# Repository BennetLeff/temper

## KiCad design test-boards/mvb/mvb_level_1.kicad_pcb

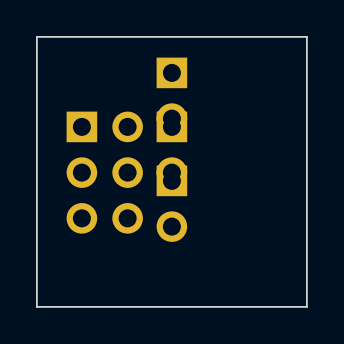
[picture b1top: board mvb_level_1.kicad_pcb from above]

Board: 2 copper layers, 15.0 x 15.0 mm, 4 parts (0 on the bottom side), 6 nets, no tracks yet.

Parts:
J1: PinHeader_2x04_P2.54mm_Vertical
J2, J3, J4: PinHeader_1x02_P2.54mm_Vertical

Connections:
GND: J1.1, J2.1
SIG1: J1.3, J2.2
SIG2: J1.4, J3.2
SIG3: J1.5, J4.1
SIG4: J1.6, J4.2
VCC: J1.2, J3.1

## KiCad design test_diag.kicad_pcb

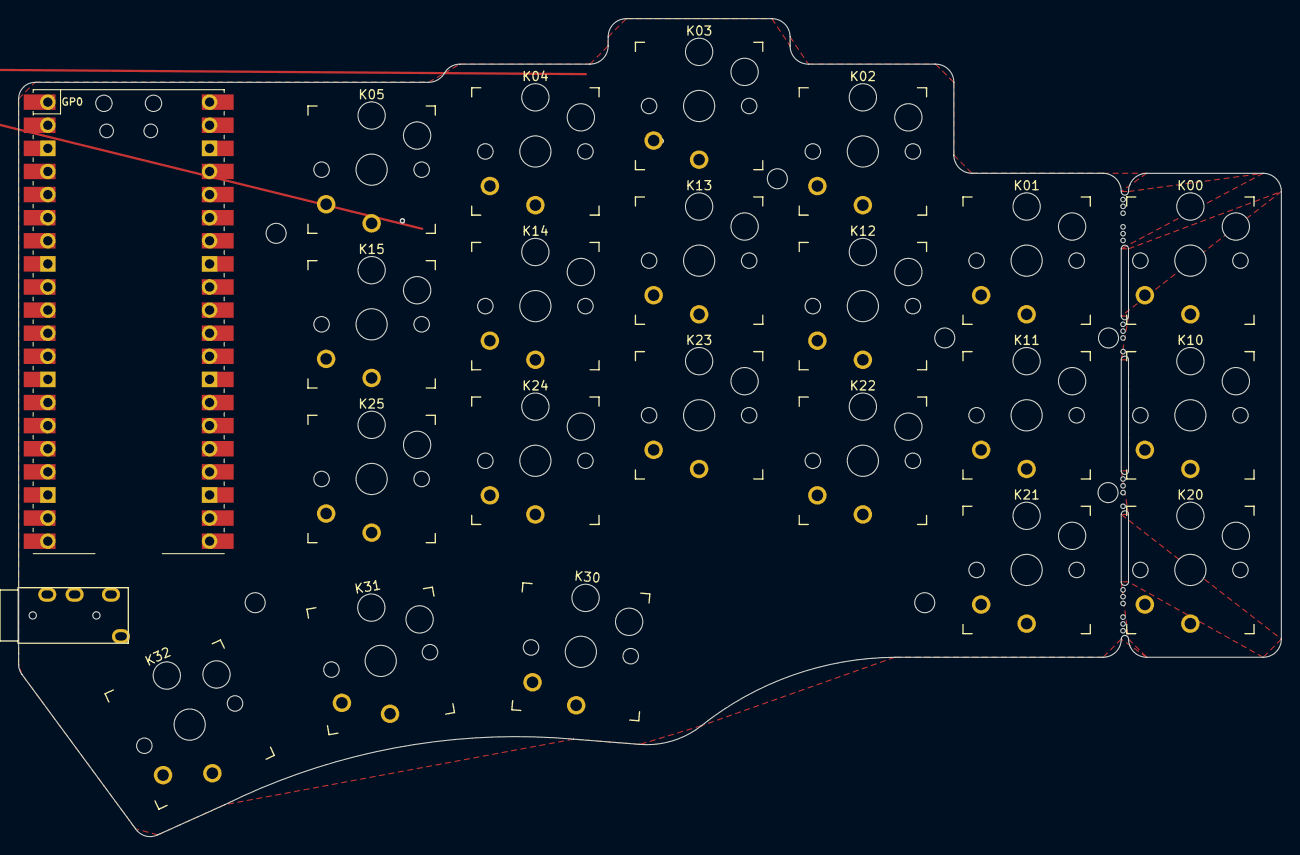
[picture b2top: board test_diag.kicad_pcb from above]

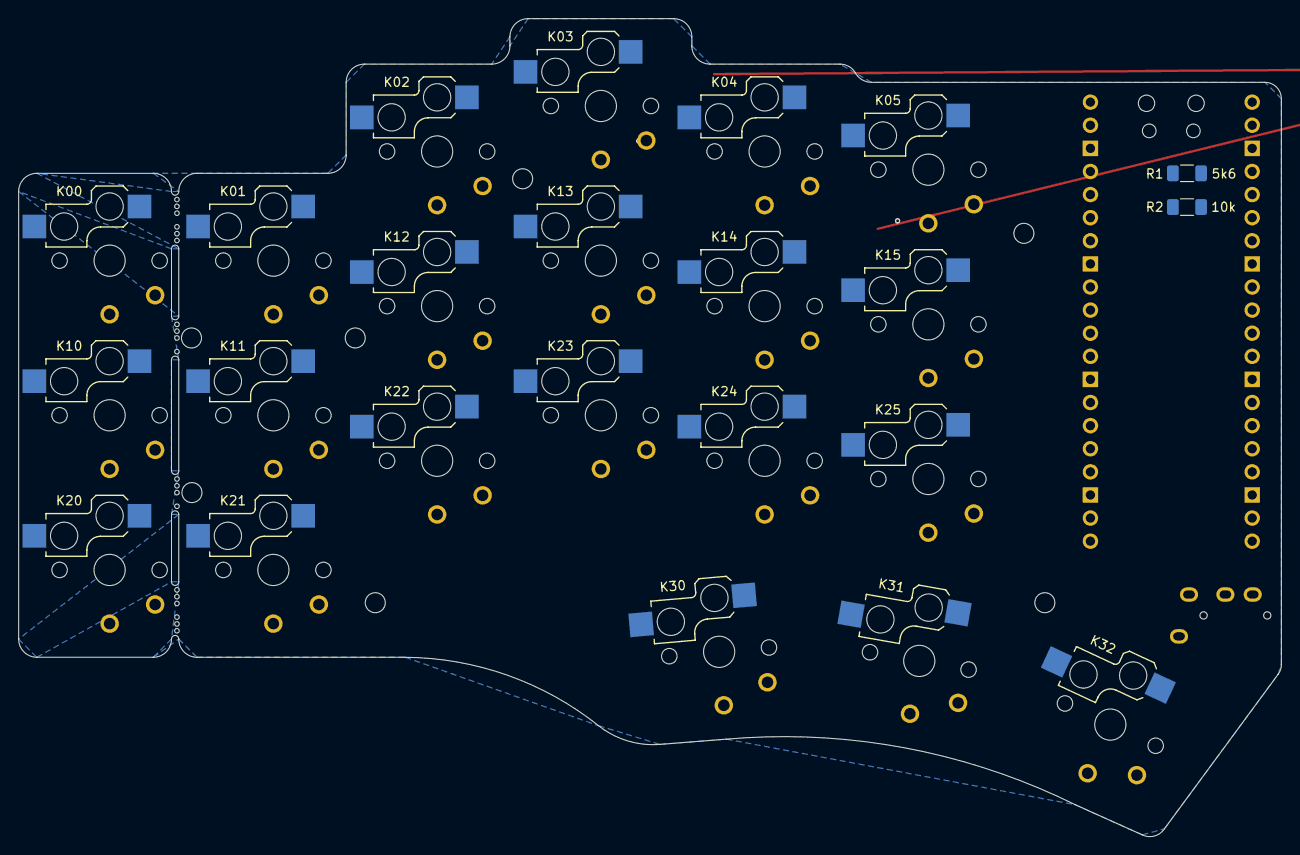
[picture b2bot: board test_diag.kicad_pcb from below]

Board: 2 copper layers, 138.8 x 89.9 mm, 36 parts (13 on the bottom side), 27 nets.

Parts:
H1, H1#2, H2, H3, H4, H4#2, H4#3: MountingHole; MountingHole_2.2mm_M2-8mm
J1: TRRS; TRRS-PJ-320A
K00, K01, K02, K03, K04, K05, K10, K11, K12, K13, K14, K15, K20, K21, K22, K23, K24, K25, K30, K31, K32: KEYSW; Kailh_socket_PG1350_optional
MB1, MB2: MountingHole; mousebites_2
MB3, MB4: MountingHole; mousebites_3
R1: 5k6; R_1206_3216Metric_Pad1.30x1.75mm_HandSolder
R2: 10k; R_1206_3216Metric_Pad1.30x1.75mm_HandSolder
U2: Pico; RPi_Pico_SMD_TH

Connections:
/k00: K00.1, U2.15 (GPIO11)
/k01: K01.1, U2.11 (GPIO8)
/k02: K02.1, U2.7 (GPIO5)
/k03: K03.1, U2.4 (GPIO2)
/k04: K04.1, U2.27 (GPIO21)
/k05: K05.1, U2.29 (GPIO22)
/k10: K10.1, U2.16 (GPIO12)
/k11: K11.1, U2.12 (GPIO9)
/k12: K12.1, U2.9 (GPIO6)
/k13: K13.1, U2.5 (GPIO3)
/k14: K14.1, U2.25 (GPIO19)
/k15: K15.1, U2.26 (GPIO20)
/k20: K20.1, U2.17 (GPIO13)
/k21: K21.1, U2.14 (GPIO10)
/k22: K22.1, U2.10 (GPIO7)
/k23: K23.1, U2.6 (GPIO4)
/k24: K24.1, U2.22 (GPIO17)
/k25: K25.1, U2.24 (GPIO18)
/k30: K30.1, U2.21 (GPIO16)
/k31: K31.1, U2.19 (GPIO14)
/k32: K32.1, U2.20 (GPIO15)
GND: J1.3 (RING1), K00.2, K01.2, K02.2, K03.2, K04.2, K05.2, K10.2, K11.2, K12.2, K13.2, K14.2, K15.2, K20.2, K21.2, K22.2, K23.2, K24.2, K25.2, K30.2, K31.2, K32.2, R2.2, U2.3 (GND), U2.8 (GND), U2.13 (GND), U2.18 (GND), U2.23 (GND), U2.28 (GND), U2.33 (AGND), U2.38 (GND)
VBUS: R1.1, U2.40 (VBUS)
VCC: J1.2 (TIP), U2.39 (VSYS)
rx: J1.4 (RING2), U2.2 (GPIO1)
tx: J1.1 (SLEEVE), U2.1 (GPIO0)
vbus_sense: R1.2, R2.1, U2.34 (GPIO28_ADC2)
